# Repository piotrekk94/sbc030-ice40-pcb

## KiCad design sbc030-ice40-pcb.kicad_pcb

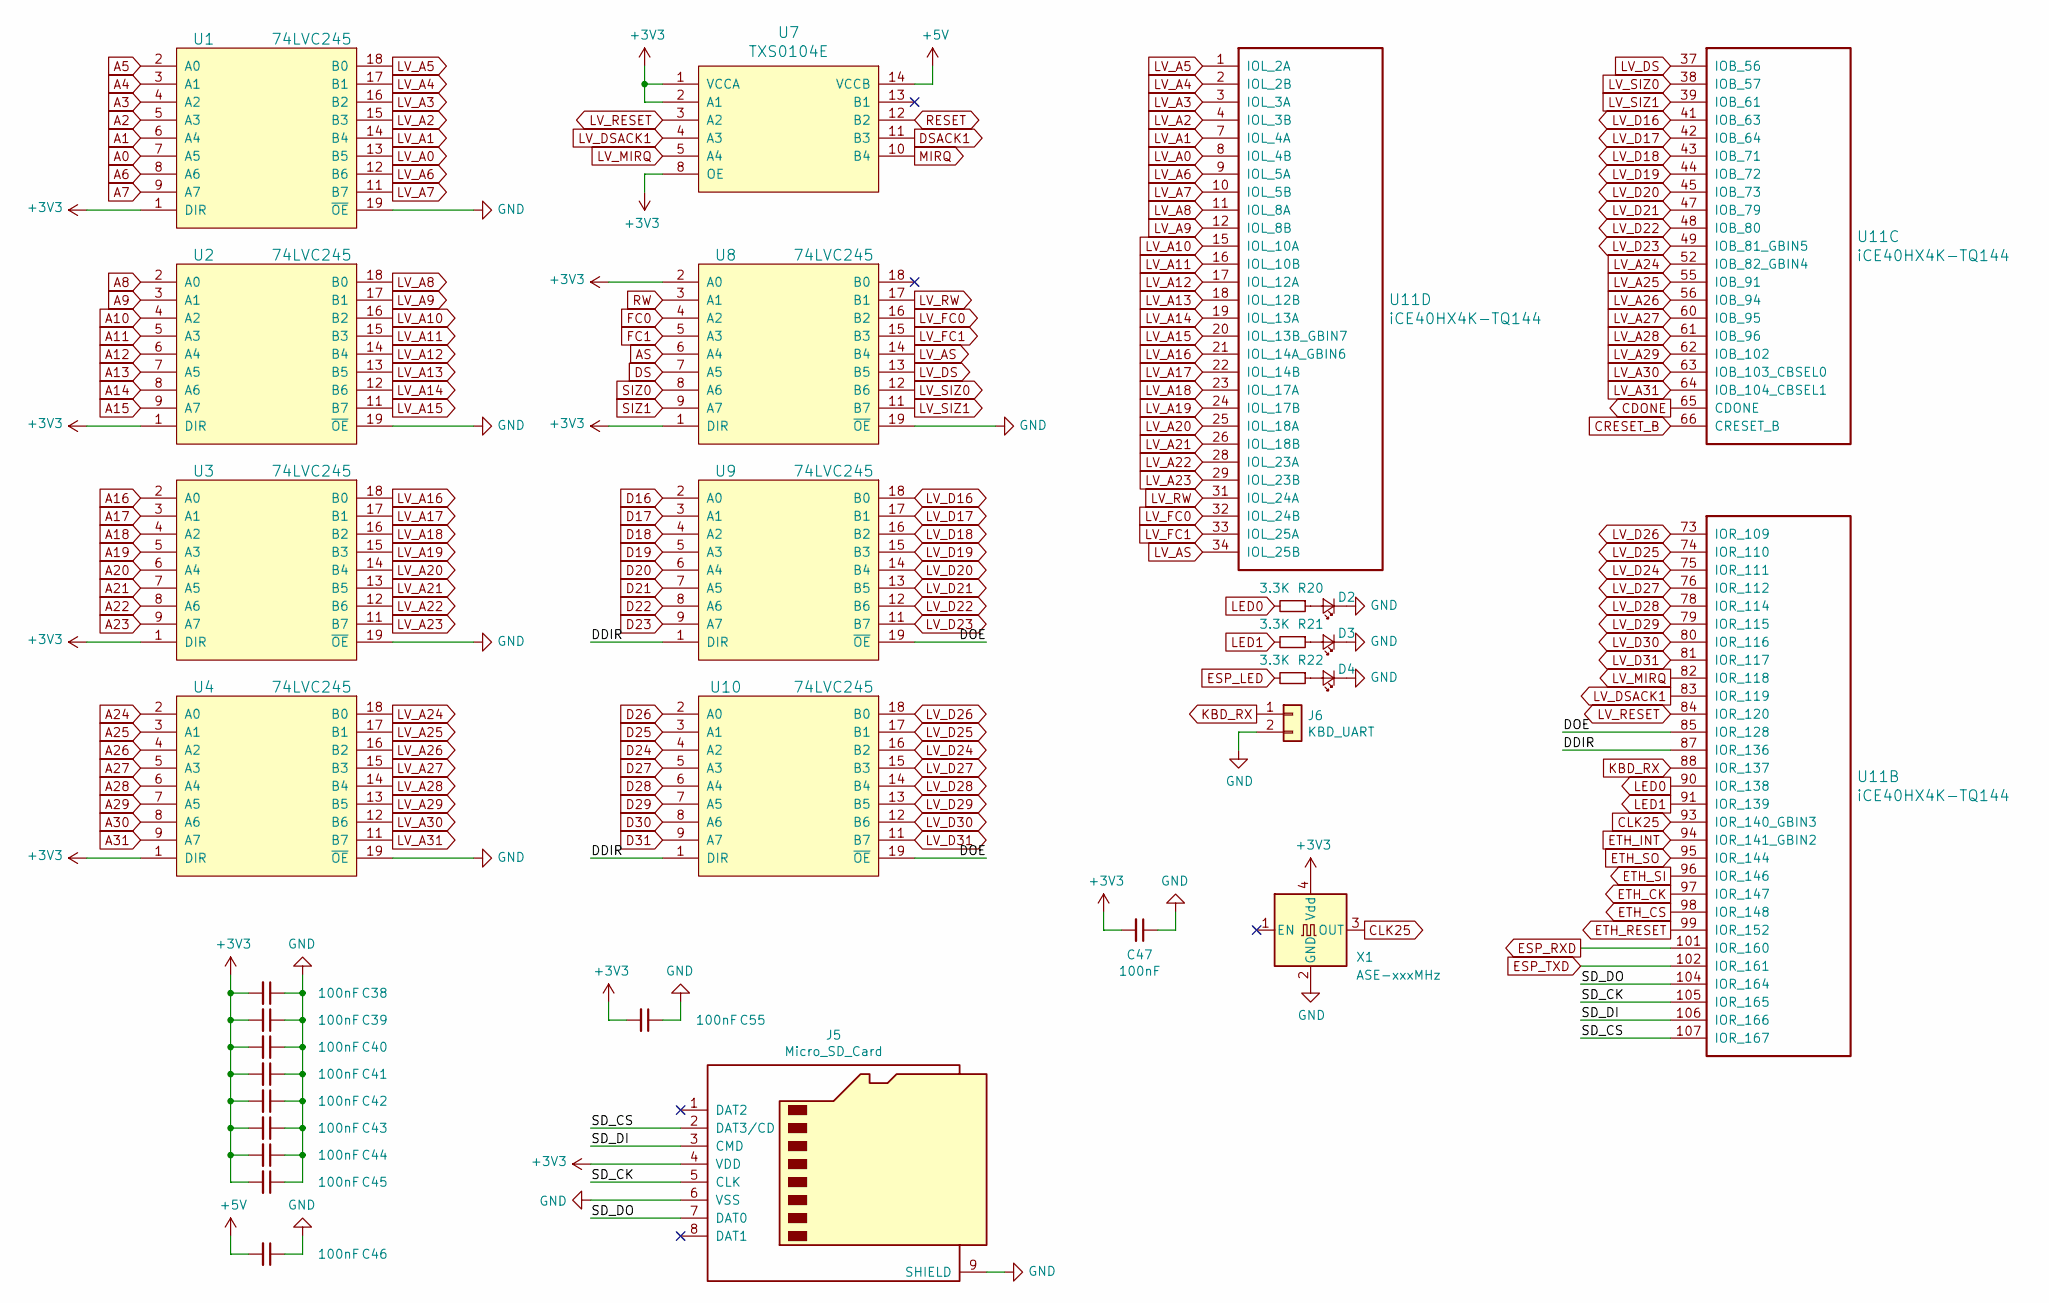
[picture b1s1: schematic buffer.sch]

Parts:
C38, C39, C40, C41, C42, C43, C44, C45, C46, C47, C55: 100nF; C_0603_1608Metric
D2, D3, D4: LED_Small; LED_0603_1608Metric
J5: Micro_SD_Card; microSD_HC_Wuerth_693072010801
J6: KBD_UART; PinHeader_1x02_P2.54mm_Vertical
R20, R21, R22: 3.3K; R_0603_1608Metric
U1, U2, U3, U4, U8, U9, U10: 74LVC245; TSSOP-20_4.4x6.5mm_P0.65mm
U7: TXS0104E; TSSOP-14_4.4x5mm_P0.65mm
U11: iCE40HX4K-TQ144; LQFP-144_20x20mm_P0.5mm
X1: ASE-xxxMHz; Oscillator_SMD_Abracon_ASE-4Pin_3.2x2.5mm

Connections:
+3V3: C38.2, C39.2, C40.2, C41.2, C42.2, C43.2, C44.2, C45.2, C47.2, C55.2, J5.4 (VDD), U1.1 (DIR), U1.20 (VCC), U2.1 (DIR), U2.20 (VCC), U3.1 (DIR), U3.20 (VCC), U4.1 (DIR), U4.20 (VCC), U7.1 (VCCA), U7.2 (A1), U7.8 (OE), U8.1 (DIR), U8.2 (A0), U8.20 (VCC), U9.20 (VCC), U10.20 (VCC), X1.4 (Vdd); also elsewhere on the board
+5V: C46.2, U7.14 (VCCB); also elsewhere on the board
/IO Buffers/DDIR: U9.1 (DIR), U10.1 (DIR), U11.87 (IOR_136)
/IO Buffers/DOE: U9.19 (~OE), U10.19 (~OE), U11.85 (IOR_128)
/IO Buffers/SD_CK: J5.5 (CLK), U11.105 (IOR_165)
/IO Buffers/SD_CS: J5.2 (DAT3/CD), U11.107 (IOR_167)
/IO Buffers/SD_DI: J5.3 (CMD), U11.106 (IOR_166)
/IO Buffers/SD_DO: J5.7 (DAT0), U11.104 (IOR_164)
A0: U1.7 (A5); also elsewhere on the board
A1: U1.6 (A4); also elsewhere on the board
A2: U1.5 (A3); also elsewhere on the board
A3: U1.4 (A2); also elsewhere on the board
A4: U1.3 (A1); also elsewhere on the board
A5: U1.2 (A0); also elsewhere on the board
A6: U1.8 (A6); also elsewhere on the board
A7: U1.9 (A7); also elsewhere on the board
A8: U2.2 (A0); also elsewhere on the board
A9: U2.3 (A1); also elsewhere on the board
A10: U2.4 (A2); also elsewhere on the board
A11: U2.5 (A3); also elsewhere on the board
A12: U2.6 (A4); also elsewhere on the board
A13: U2.7 (A5); also elsewhere on the board
A14: U2.8 (A6); also elsewhere on the board
A15: U2.9 (A7); also elsewhere on the board
A16: U3.2 (A0); also elsewhere on the board
A17: U3.3 (A1); also elsewhere on the board
A18: U3.4 (A2); also elsewhere on the board
A19: U3.5 (A3); also elsewhere on the board
A20: U3.6 (A4); also elsewhere on the board
A21: U3.7 (A5); also elsewhere on the board
A22: U3.8 (A6); also elsewhere on the board
A23: U3.9 (A7); also elsewhere on the board
A24: U4.2 (A0); also elsewhere on the board
A25: U4.3 (A1); also elsewhere on the board
A26: U4.4 (A2); also elsewhere on the board
A27: U4.5 (A3); also elsewhere on the board
A28: U4.6 (A4); also elsewhere on the board
A29: U4.7 (A5); also elsewhere on the board
A30: U4.8 (A6); also elsewhere on the board
A31: U4.9 (A7); also elsewhere on the board
AS: U8.6 (A4); also elsewhere on the board
CDONE: U11.65 (CDONE); also elsewhere on the board
CLK25: U11.93 (IOR_140_GBIN3), X1.3 (OUT); also elsewhere on the board
CRESET_B: U11.66 (CRESET_B); also elsewhere on the board
D16: U9.2 (A0); also elsewhere on the board
D17: U9.3 (A1); also elsewhere on the board
D18: U9.4 (A2); also elsewhere on the board
D19: U9.5 (A3); also elsewhere on the board
D20: U9.6 (A4); also elsewhere on the board
D21: U9.7 (A5); also elsewhere on the board
D22: U9.8 (A6); also elsewhere on the board
D23: U9.9 (A7); also elsewhere on the board
D24: U10.4 (A2); also elsewhere on the board
D25: U10.3 (A1); also elsewhere on the board
D26: U10.2 (A0); also elsewhere on the board
D27: U10.5 (A3); also elsewhere on the board
D28: U10.6 (A4); also elsewhere on the board
D29: U10.7 (A5); also elsewhere on the board
D30: U10.8 (A6); also elsewhere on the board
D31: U10.9 (A7); also elsewhere on the board
DS: U8.7 (A5); also elsewhere on the board
DSACK1: U7.11 (B3); also elsewhere on the board
ESP_LED: R22.2; also elsewhere on the board
ESP_RXD: U11.101 (IOR_160); also elsewhere on the board
ESP_TXD: U11.102 (IOR_161); also elsewhere on the board
ETH_CK: U11.97 (IOR_147); also elsewhere on the board
ETH_CS: U11.98 (IOR_148); also elsewhere on the board
ETH_INT: U11.94 (IOR_141_GBIN2); also elsewhere on the board
ETH_RESET: U11.99 (IOR_152); also elsewhere on the board
ETH_SI: U11.96 (IOR_146); also elsewhere on the board
ETH_SO: U11.95 (IOR_144); also elsewhere on the board
FC0: U8.4 (A2); also elsewhere on the board
FC1: U8.5 (A3); also elsewhere on the board
GND: C38.1, C39.1, C40.1, C41.1, C42.1, C43.1, C44.1, C45.1, C46.1, C47.1, C55.1, D2.1 (K), D3.1 (K), D4.1 (K), J5.6 (VSS), J5.9 (SHIELD), J6.2, U1.10 (GND), U1.19 (~OE), U2.10 (GND), U2.19 (~OE), U3.10 (GND), U3.19 (~OE), U4.10 (GND), U4.19 (~OE), U7.7 (GND), U8.10 (GND), U8.19 (~OE), U9.10 (GND), U10.10 (GND), X1.2 (GND); also elsewhere on the board
KBD_RX: J6.1, U11.88 (IOR_137)
LED0: R20.2, U11.90 (IOR_138)
LED1: R21.2, U11.91 (IOR_139)
LV_A0: U1.13 (B5), U11.8 (IOL_4B)
LV_A1: U1.14 (B4), U11.7 (IOL_4A)
LV_A2: U1.15 (B3), U11.4 (IOL_3B)
LV_A3: U1.16 (B2), U11.3 (IOL_3A)
LV_A4: U1.17 (B1), U11.2 (IOL_2B)
LV_A5: U1.18 (B0), U11.1 (IOL_2A)
LV_A6: U1.12 (B6), U11.9 (IOL_5A)
LV_A7: U1.11 (B7), U11.10 (IOL_5B)
LV_A8: U2.18 (B0), U11.11 (IOL_8A)
LV_A9: U2.17 (B1), U11.12 (IOL_8B)
LV_A10: U2.16 (B2), U11.15 (IOL_10A)
LV_A11: U2.15 (B3), U11.16 (IOL_10B)
LV_A12: U2.14 (B4), U11.17 (IOL_12A)
LV_A13: U2.13 (B5), U11.18 (IOL_12B)
LV_A14: U2.12 (B6), U11.19 (IOL_13A)
LV_A15: U2.11 (B7), U11.20 (IOL_13B_GBIN7)
LV_A16: U3.18 (B0), U11.21 (IOL_14A_GBIN6)
LV_A17: U3.17 (B1), U11.22 (IOL_14B)
LV_A18: U3.16 (B2), U11.23 (IOL_17A)
LV_A19: U3.15 (B3), U11.24 (IOL_17B)
LV_A20: U3.14 (B4), U11.25 (IOL_18A)
LV_A21: U3.13 (B5), U11.26 (IOL_18B)
LV_A22: U3.12 (B6), U11.28 (IOL_23A)
LV_A23: U3.11 (B7), U11.29 (IOL_23B)
LV_A24: U4.18 (B0), U11.52 (IOB_82_GBIN4)
LV_A25: U4.17 (B1), U11.55 (IOB_91)
LV_A26: U4.16 (B2), U11.56 (IOB_94)
LV_A27: U4.15 (B3), U11.60 (IOB_95)
LV_A28: U4.14 (B4), U11.61 (IOB_96)
LV_A29: U4.13 (B5), U11.62 (IOB_102)
LV_A30: U4.12 (B6), U11.63 (IOB_103_CBSEL0)
LV_A31: U4.11 (B7), U11.64 (IOB_104_CBSEL1)
LV_AS: U8.14 (B4), U11.34 (IOL_25B)
LV_D16: U9.18 (B0), U11.41 (IOB_63)
LV_D17: U9.17 (B1), U11.42 (IOB_64)
LV_D18: U9.16 (B2), U11.43 (IOB_71)
LV_D19: U9.15 (B3), U11.44 (IOB_72)
LV_D20: U9.14 (B4), U11.45 (IOB_73)
LV_D21: U9.13 (B5), U11.47 (IOB_79)
LV_D22: U9.12 (B6), U11.48 (IOB_80)
LV_D23: U9.11 (B7), U11.49 (IOB_81_GBIN5)
LV_D24: U10.16 (B2), U11.75 (IOR_111)
LV_D25: U10.17 (B1), U11.74 (IOR_110)
LV_D26: U10.18 (B0), U11.73 (IOR_109)
LV_D27: U10.15 (B3), U11.76 (IOR_112)
LV_D28: U10.14 (B4), U11.78 (IOR_114)
LV_D29: U10.13 (B5), U11.79 (IOR_115)
LV_D30: U10.12 (B6), U11.80 (IOR_116)
LV_D31: U10.11 (B7), U11.81 (IOR_117)
LV_DS: U8.13 (B5), U11.37 (IOB_56)
LV_DSACK1: U7.4 (A3), U11.83 (IOR_119)
LV_FC0: U8.16 (B2), U11.32 (IOL_24B)
LV_FC1: U8.15 (B3), U11.33 (IOL_25A)
LV_MIRQ: U7.5 (A4), U11.82 (IOR_118)
LV_RESET: U7.3 (A2), U11.84 (IOR_120)
LV_RW: U8.17 (B1), U11.31 (IOL_24A)
LV_SIZ0: U8.12 (B6), U11.38 (IOB_57)
LV_SIZ1: U8.11 (B7), U11.39 (IOB_61)
MIRQ: U7.10 (B4); also elsewhere on the board
unnamed: D2.2 (A), R20.1
unnamed: D3.2 (A), R21.1
unnamed: D4.2 (A), R22.1
RESET: U7.12 (B2); also elsewhere on the board
RW: U8.3 (A1); also elsewhere on the board
SIZ0: U8.8 (A6); also elsewhere on the board
SIZ1: U8.9 (A7); also elsewhere on the board

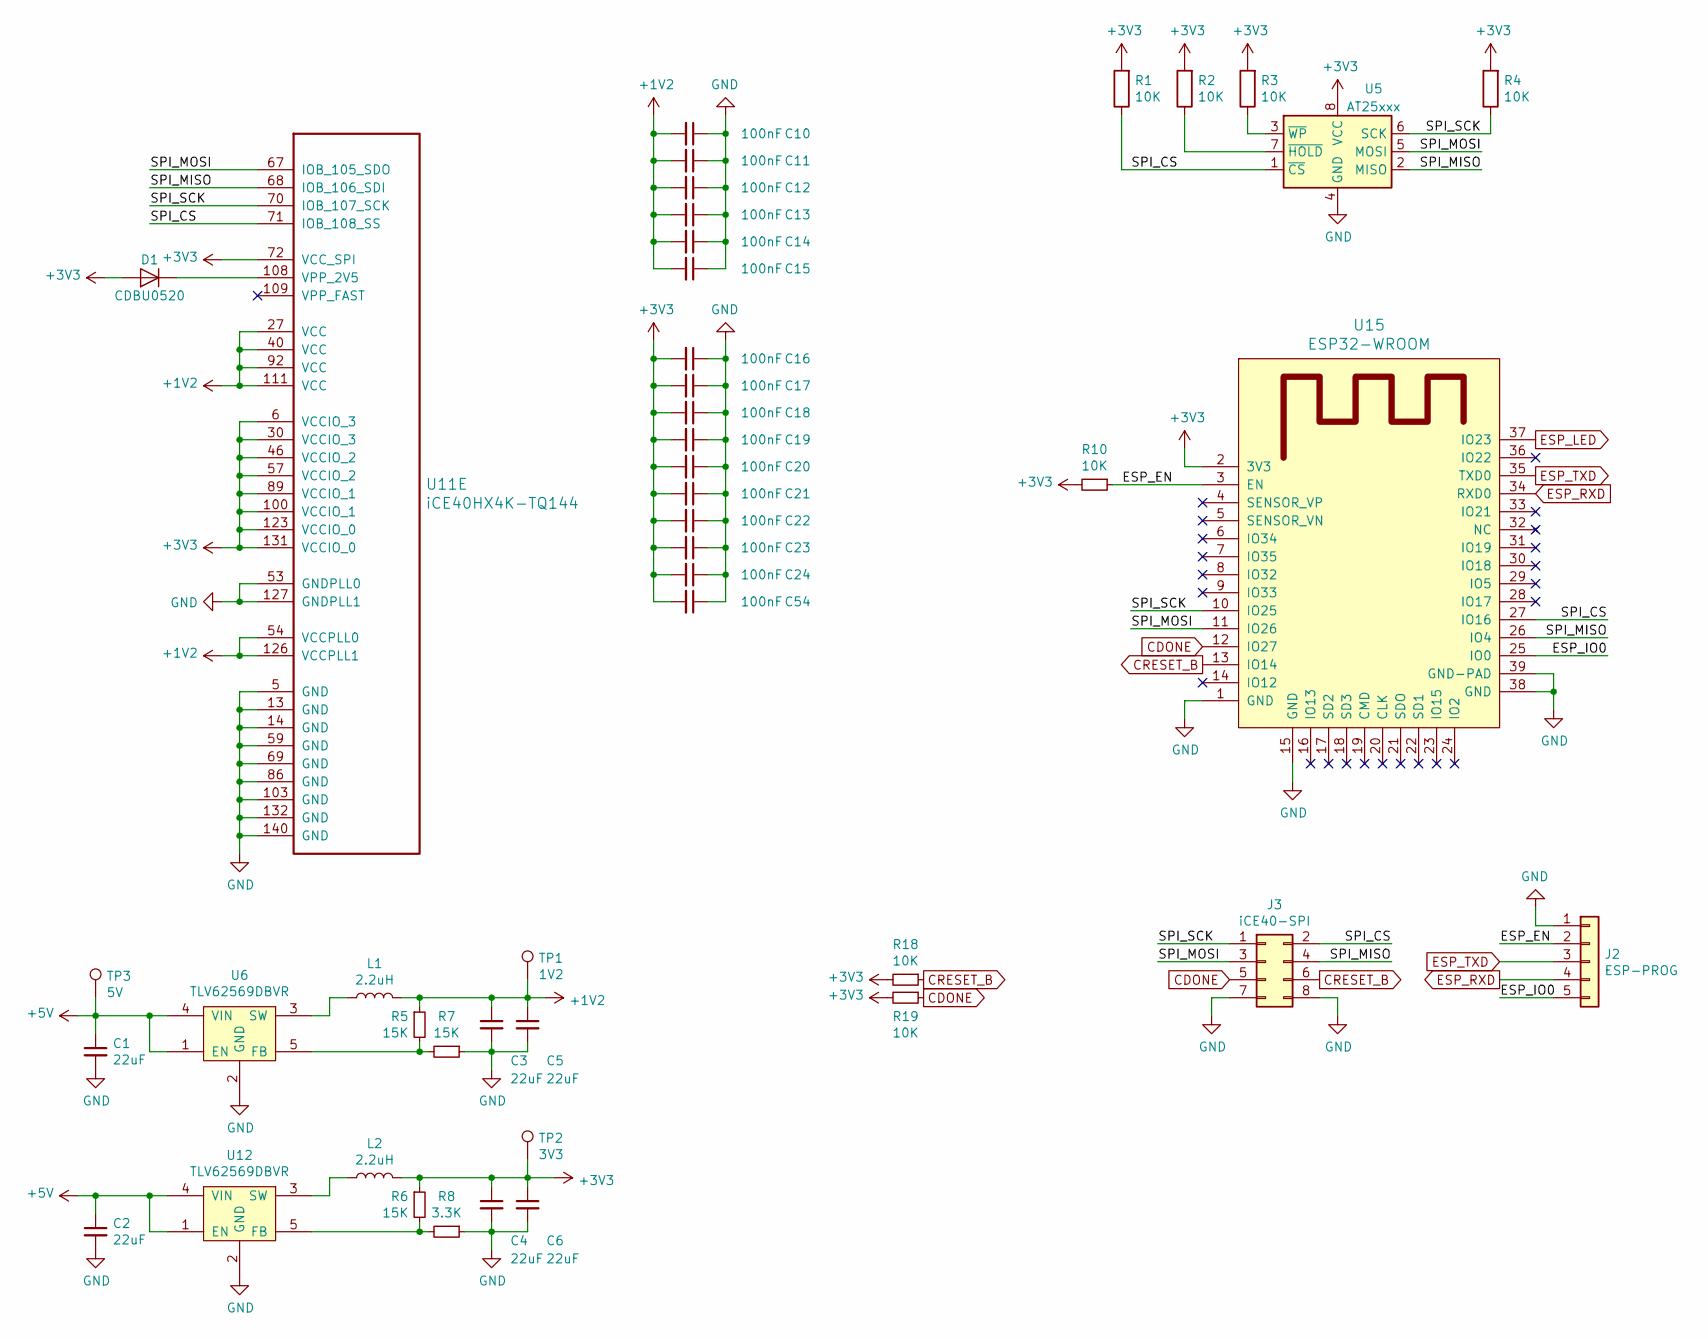
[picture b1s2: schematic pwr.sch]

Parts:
C1, C2, C3, C4, C5, C6: 22uF; C_0805_2012Metric
C10, C11, C12, C13, C14, C15, C16, C17, C18, C19, C20, C21, C22, C23, C24, C54: 100nF; C_0603_1608Metric
D1: CDBU0520; D_0603_1608Metric
J2: ESP-PROG; PinHeader_1x05_P2.54mm_Vertical
J3: iCE40-SPI; PinHeader_2x04_P2.54mm_Vertical
L1, L2: 2.2uH; L_1210_3225Metric
R1, R2, R3, R4, R10, R18, R19: 10K; R_0603_1608Metric
R5, R6, R7: 15K; R_0603_1608Metric
R8: 3.3K; R_0603_1608Metric
TP1: 1V2; TestPoint_Loop_D2.50mm_Drill1.0mm_LowProfile
TP2: 3V3; TestPoint_Loop_D2.50mm_Drill1.0mm_LowProfile
TP3: 5V; TestPoint_Loop_D2.50mm_Drill1.0mm_LowProfile
U5: AT25xxx; SOIC-8_3.9x4.9mm_P1.27mm
U6, U12: TLV62569DBVR; SOT-23-5
U11: iCE40HX4K-TQ144; LQFP-144_20x20mm_P0.5mm
U15: ESP32-WROOM

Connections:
+1V2: C3.1, C5.1, C10.2, C11.2, C12.2, C13.2, C14.2, C15.2, L1.2, R5.1, TP1.1, U11.27 (VCC), U11.40 (VCC), U11.54 (VCCPLL0), U11.92 (VCC), U11.111 (VCC), U11.126 (VCCPLL1)
+3V3: C4.1, C6.1, C16.2, C17.2, C18.2, C19.2, C20.2, C21.2, C22.2, C23.2, C24.2, C54.2, D1.2 (A), L2.2, R1.2, R2.2, R3.2, R4.2, R6.1, R10.2, R18.2, R19.2, TP2.1, U5.8 (VCC), U11.6 (VCCIO_3), U11.30 (VCCIO_3), U11.46 (VCCIO_2), U11.57 (VCCIO_2), U11.72 (VCC_SPI), U11.89 (VCCIO_1), U11.100 (VCCIO_1), U11.123 (VCCIO_0), U11.131 (VCCIO_0), U15.2 (3V3); also elsewhere on the board
+5V: C1.1, C2.1, TP3.1, U6.1 (EN), U6.4 (VIN), U12.1 (EN), U12.4 (VIN); also elsewhere on the board
/Power & Flash/ESP_EN: J2.2, R10.1, U15.3 (EN)
/Power & Flash/ESP_IO0: J2.5, U15.25 (IO0)
/Power & Flash/SPI_CS: J3.2, R1.1, U5.1 (~CS), U11.71 (IOB_108_SS), U15.27 (IO16)
/Power & Flash/SPI_MISO: J3.4, U5.2 (MISO), U11.68 (IOB_106_SDI), U15.26 (IO4)
/Power & Flash/SPI_MOSI: J3.3, U5.5 (MOSI), U11.67 (IOB_105_SDO), U15.11 (IO26)
/Power & Flash/SPI_SCK: J3.1, R4.1, U5.6 (SCK), U11.70 (IOB_107_SCK), U15.10 (IO25)
CDONE: J3.5, R19.1, U15.12 (IO27); also elsewhere on the board
CRESET_B: J3.6, R18.1, U15.13 (IO14); also elsewhere on the board
ESP_LED: U15.37 (IO23); also elsewhere on the board
ESP_RXD: J2.4, U15.34 (RXD0); also elsewhere on the board
ESP_TXD: J2.3, U15.35 (TXD0); also elsewhere on the board
GND: C1.2, C2.2, C3.2, C4.2, C5.2, C6.2, C10.1, C11.1, C12.1, C13.1, C14.1, C15.1, C16.1, C17.1, C18.1, C19.1, C20.1, C21.1, C22.1, C23.1, C24.1, C54.1, J2.1, J3.7, J3.8, R7.1, R8.1, U5.4 (GND), U6.2 (GND), U11.5 (GND), U11.13 (GND), U11.14 (GND), U11.53 (GNDPLL0), U11.59 (GND), U11.69 (GND), U11.86 (GND), U11.103 (GND), U11.127 (GNDPLL1), U11.132 (GND), U11.140 (GND), U12.2 (GND), U15.1 (GND), U15.15 (GND), U15.38 (GND), U15.39 (GND-PAD); also elsewhere on the board
unnamed: D1.1 (K), U11.108 (VPP_2V5)
unnamed: L1.1, U6.3 (SW)
unnamed: L2.1, U12.3 (SW)
unnamed: R2.1, U5.7 (~HOLD)
unnamed: R3.1, U5.3 (~WP)
unnamed: R5.2, R7.2, U6.5 (FB)
unnamed: R6.2, R8.2, U12.5 (FB)

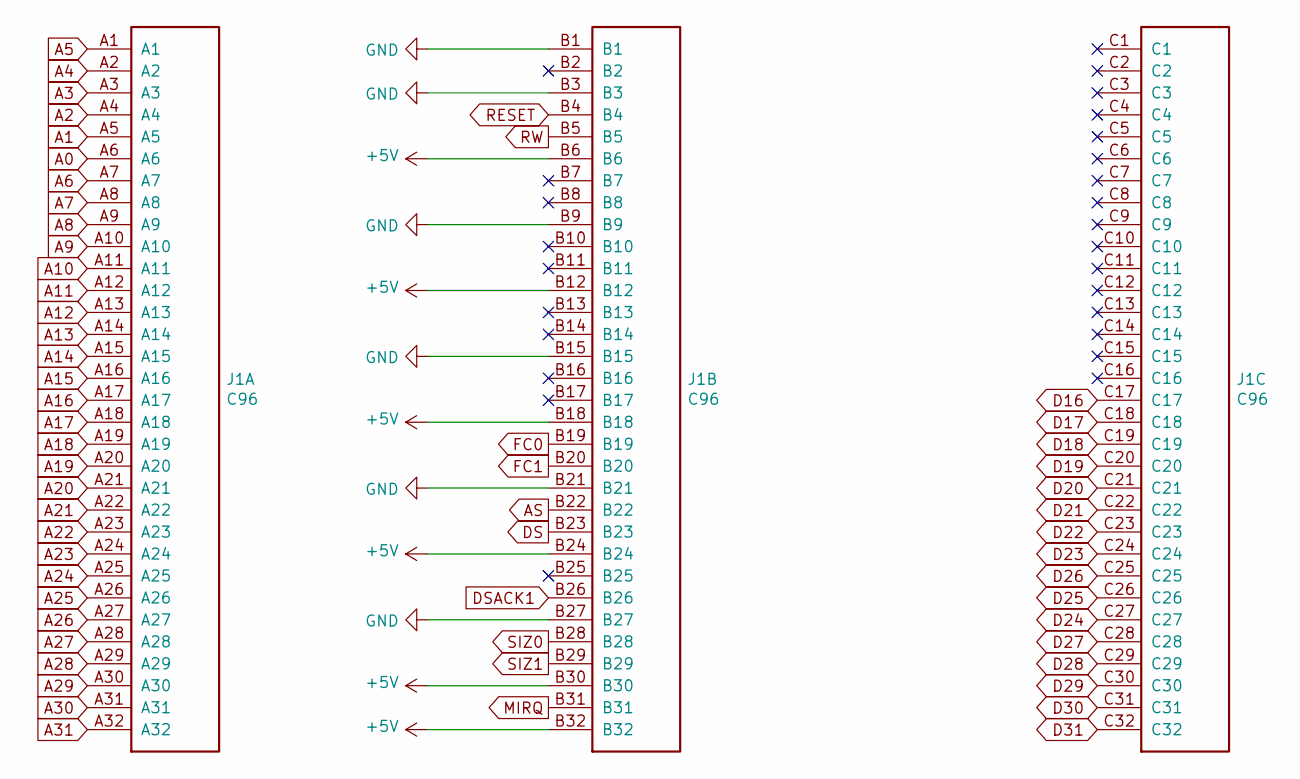
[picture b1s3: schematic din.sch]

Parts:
J1: C96; C96ABCM

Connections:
+5V: J1.B6, J1.B12, J1.B18, J1.B24, J1.B30, J1.B32; also elsewhere on the board
A0: J1.A6; also elsewhere on the board
A1: J1.A5; also elsewhere on the board
A2: J1.A4; also elsewhere on the board
A3: J1.A3; also elsewhere on the board
A4: J1.A2; also elsewhere on the board
A5: J1.A1; also elsewhere on the board
A6: J1.A7; also elsewhere on the board
A7: J1.A8; also elsewhere on the board
A8: J1.A9; also elsewhere on the board
A9: J1.A10; also elsewhere on the board
A10: J1.A11; also elsewhere on the board
A11: J1.A12; also elsewhere on the board
A12: J1.A13; also elsewhere on the board
A13: J1.A14; also elsewhere on the board
A14: J1.A15; also elsewhere on the board
A15: J1.A16; also elsewhere on the board
A16: J1.A17; also elsewhere on the board
A17: J1.A18; also elsewhere on the board
A18: J1.A19; also elsewhere on the board
A19: J1.A20; also elsewhere on the board
A20: J1.A21; also elsewhere on the board
A21: J1.A22; also elsewhere on the board
A22: J1.A23; also elsewhere on the board
A23: J1.A24; also elsewhere on the board
A24: J1.A25; also elsewhere on the board
A25: J1.A26; also elsewhere on the board
A26: J1.A27; also elsewhere on the board
A27: J1.A28; also elsewhere on the board
A28: J1.A29; also elsewhere on the board
A29: J1.A30; also elsewhere on the board
A30: J1.A31; also elsewhere on the board
A31: J1.A32; also elsewhere on the board
AS: J1.B22; also elsewhere on the board
D16: J1.C17; also elsewhere on the board
D17: J1.C18; also elsewhere on the board
D18: J1.C19; also elsewhere on the board
D19: J1.C20; also elsewhere on the board
D20: J1.C21; also elsewhere on the board
D21: J1.C22; also elsewhere on the board
D22: J1.C23; also elsewhere on the board
D23: J1.C24; also elsewhere on the board
D24: J1.C27; also elsewhere on the board
D25: J1.C26; also elsewhere on the board
D26: J1.C25; also elsewhere on the board
D27: J1.C28; also elsewhere on the board
D28: J1.C29; also elsewhere on the board
D29: J1.C30; also elsewhere on the board
D30: J1.C31; also elsewhere on the board
D31: J1.C32; also elsewhere on the board
DS: J1.B23; also elsewhere on the board
DSACK1: J1.B26; also elsewhere on the board
FC0: J1.B19; also elsewhere on the board
FC1: J1.B20; also elsewhere on the board
GND: J1.B1, J1.B3, J1.B9, J1.B15, J1.B21, J1.B27; also elsewhere on the board
MIRQ: J1.B31; also elsewhere on the board
RESET: J1.B4; also elsewhere on the board
RW: J1.B5; also elsewhere on the board
SIZ0: J1.B28; also elsewhere on the board
SIZ1: J1.B29; also elsewhere on the board

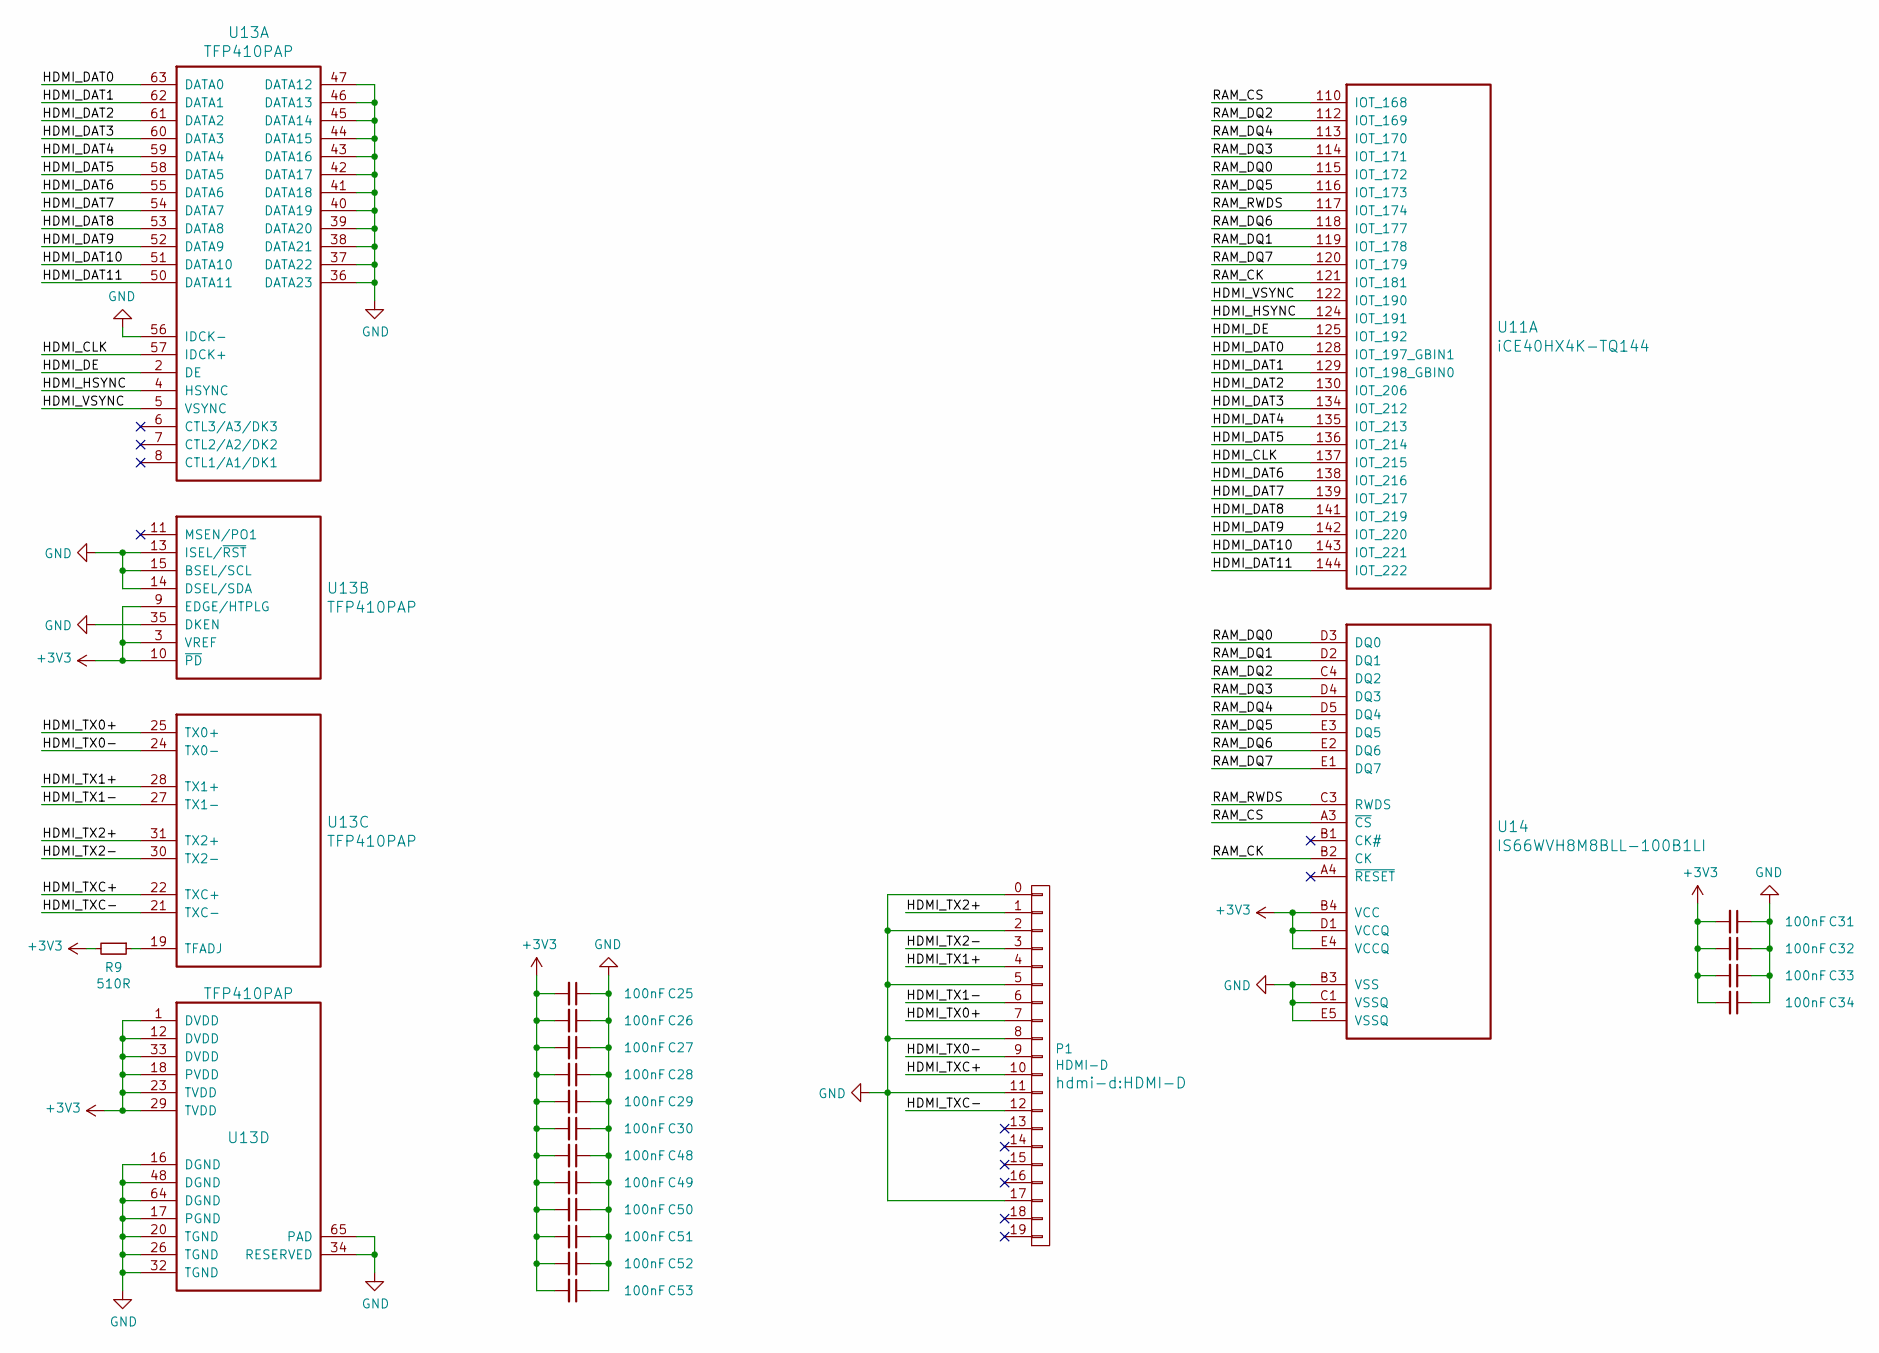
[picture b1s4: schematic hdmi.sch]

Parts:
C25, C26, C27, C28, C29, C30, C31, C32, C33, C34, C48, C49, C50, C51, C52, C53: 100nF; C_0603_1608Metric
P1: HDMI-D
R9: 510R; R_0603_1608Metric
U11: iCE40HX4K-TQ144; LQFP-144_20x20mm_P0.5mm
U13: TFP410PAP; LQFP-64-1EP_10x10mm_P0.5mm_EP6.5x6.5mm
U14: IS66WVH8M8BLL-100B1LI; TFBGA25

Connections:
+3V3: C25.2, C26.2, C27.2, C28.2, C29.2, C30.2, C31.2, C32.2, C33.2, C34.2, C48.2, C49.2, C50.2, C51.2, C52.2, C53.2, R9.2, U13.1 (DVDD), U13.3 (VREF), U13.9 (EDGE/HTPLG), U13.10 (~PD), U13.12 (DVDD), U13.18 (PVDD), U13.23 (TVDD), U13.29 (TVDD), U13.33 (DVDD), U14.B4 (VCC), U14.D1 (VCCQ), U14.E4 (VCCQ); also elsewhere on the board
/HDMI/HDMI_CLK: U11.137 (IOT_215), U13.57 (IDCK+)
/HDMI/HDMI_DAT0: U11.128 (IOT_197_GBIN1), U13.63 (DATA0)
/HDMI/HDMI_DAT1: U11.129 (IOT_198_GBIN0), U13.62 (DATA1)
/HDMI/HDMI_DAT2: U11.130 (IOT_206), U13.61 (DATA2)
/HDMI/HDMI_DAT3: U11.134 (IOT_212), U13.60 (DATA3)
/HDMI/HDMI_DAT4: U11.135 (IOT_213), U13.59 (DATA4)
/HDMI/HDMI_DAT5: U11.136 (IOT_214), U13.58 (DATA5)
/HDMI/HDMI_DAT6: U11.138 (IOT_216), U13.55 (DATA6)
/HDMI/HDMI_DAT7: U11.139 (IOT_217), U13.54 (DATA7)
/HDMI/HDMI_DAT8: U11.141 (IOT_219), U13.53 (DATA8)
/HDMI/HDMI_DAT9: U11.142 (IOT_220), U13.52 (DATA9)
/HDMI/HDMI_DAT10: U11.143 (IOT_221), U13.51 (DATA10)
/HDMI/HDMI_DAT11: U11.144 (IOT_222), U13.50 (DATA11)
/HDMI/HDMI_DE: U11.125 (IOT_192), U13.2 (DE)
/HDMI/HDMI_HSYNC: U11.124 (IOT_191), U13.4 (HSYNC)
/HDMI/HDMI_TX0+: P1.7, U13.25 (TX0+)
/HDMI/HDMI_TX0-: P1.9, U13.24 (TX0-)
/HDMI/HDMI_TX1+: P1.4, U13.28 (TX1+)
/HDMI/HDMI_TX1-: P1.6, U13.27 (TX1-)
/HDMI/HDMI_TX2+: P1.1, U13.31 (TX2+)
/HDMI/HDMI_TX2-: P1.3, U13.30 (TX2-)
/HDMI/HDMI_TXC+: P1.10, U13.22 (TXC+)
/HDMI/HDMI_TXC-: P1.12, U13.21 (TXC-)
/HDMI/HDMI_VSYNC: U11.122 (IOT_190), U13.5 (VSYNC)
/HDMI/RAM_CK: U11.121 (IOT_181), U14.B2 (CK)
/HDMI/RAM_CS: U11.110 (IOT_168), U14.A3 (~CS)
/HDMI/RAM_DQ0: U11.115 (IOT_172), U14.D3 (DQ0)
/HDMI/RAM_DQ1: U11.119 (IOT_178), U14.D2 (DQ1)
/HDMI/RAM_DQ2: U11.112 (IOT_169), U14.C4 (DQ2)
/HDMI/RAM_DQ3: U11.114 (IOT_171), U14.D4 (DQ3)
/HDMI/RAM_DQ4: U11.113 (IOT_170), U14.D5 (DQ4)
/HDMI/RAM_DQ5: U11.116 (IOT_173), U14.E3 (DQ5)
/HDMI/RAM_DQ6: U11.118 (IOT_177), U14.E2 (DQ6)
/HDMI/RAM_DQ7: U11.120 (IOT_179), U14.E1 (DQ7)
/HDMI/RAM_RWDS: U11.117 (IOT_174), U14.C3 (RWDS)
GND: C25.1, C26.1, C27.1, C28.1, C29.1, C30.1, C31.1, C32.1, C33.1, C34.1, C48.1, C49.1, C50.1, C51.1, C52.1, C53.1, P1.0, P1.2, P1.5, P1.8, P1.11, P1.17, U13.13 (ISEL/~RST), U13.14 (DSEL/SDA), U13.15 (BSEL/SCL), U13.16 (DGND), U13.17 (PGND), U13.20 (TGND), U13.26 (TGND), U13.32 (TGND), U13.34 (RESERVED), U13.35 (DKEN), U13.36 (DATA23), U13.37 (DATA22), U13.38 (DATA21), U13.39 (DATA20), U13.40 (DATA19), U13.41 (DATA18), U13.42 (DATA17), U13.43 (DATA16), U13.44 (DATA15), U13.45 (DATA14), U13.46 (DATA13), U13.47 (DATA12), U13.48 (DGND), U13.56 (IDCK-), U13.64 (DGND), U13.65 (PAD), U14.B3 (VSS), U14.C1 (VSSQ), U14.E5 (VSSQ); also elsewhere on the board
unnamed: R9.1, U13.19 (TFADJ)

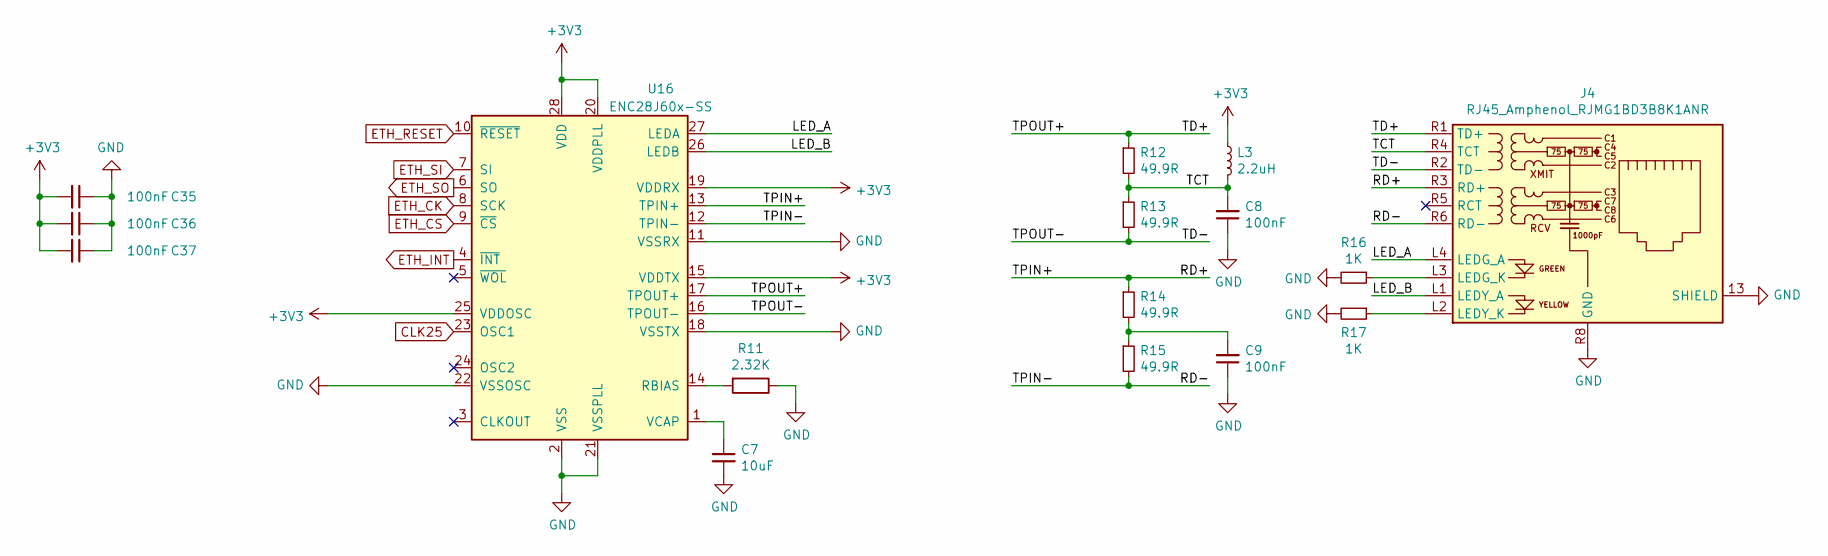
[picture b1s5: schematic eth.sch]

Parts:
C7: 10uF; C_0603_1608Metric
C8, C9, C35, C36, C37: 100nF; C_0603_1608Metric
J4: RJ45_Amphenol_RJMG1BD3B8K1ANR
L3: 2.2uH; L_1210_3225Metric
R11: 2.32K; R_0603_1608Metric
R12, R13, R14, R15: 49.9R; R_0603_1608Metric
R16, R17: 1K; R_0603_1608Metric
U16: ENC28J60x-SS; SSOP-28_5.3x10.2mm_P0.65mm

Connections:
+3V3: C35.2, C36.2, C37.2, L3.1, U16.15 (VDDTX), U16.19 (VDDRX), U16.20 (VDDPLL), U16.25 (VDDOSC), U16.28 (VDD); also elsewhere on the board
/Ethernet/LED_A: J4.L4 (LEDG_A), U16.27 (LEDA)
/Ethernet/LED_B: J4.L1 (LEDY_A), U16.26 (LEDB)
/Ethernet/RD+: J4.R3 (RD+), R14.1, U16.13 (TPIN+)
/Ethernet/RD-: J4.R6 (RD-), R15.2, U16.12 (TPIN-)
/Ethernet/TCT: C8.2, J4.R4 (TCT), L3.2, R12.2, R13.1
/Ethernet/TD+: J4.R1 (TD+), R12.1, U16.17 (TPOUT+)
/Ethernet/TD-: J4.R2 (TD-), R13.2, U16.16 (TPOUT-)
CLK25: U16.23 (OSC1); also elsewhere on the board
ETH_CK: U16.8 (SCK); also elsewhere on the board
ETH_CS: U16.9 (~CS); also elsewhere on the board
ETH_INT: U16.4 (~INT); also elsewhere on the board
ETH_RESET: U16.10 (~RESET); also elsewhere on the board
ETH_SI: U16.7 (SI); also elsewhere on the board
ETH_SO: U16.6 (SO); also elsewhere on the board
GND: C7.2, C8.1, C9.1, C35.1, C36.1, C37.1, J4.13 (SHIELD), J4.R8 (GND), R11.1, R16.2, R17.2, U16.2 (VSS), U16.11 (VSSRX), U16.18 (VSSTX), U16.21 (VSSPLL), U16.22 (VSSOSC); also elsewhere on the board
unnamed: C7.1, U16.1 (VCAP)
unnamed: C9.2, R14.2, R15.1
unnamed: J4.L2 (LEDY_K), R17.1
unnamed: J4.L3 (LEDG_K), R16.1
unnamed: R11.2, U16.14 (RBIAS)

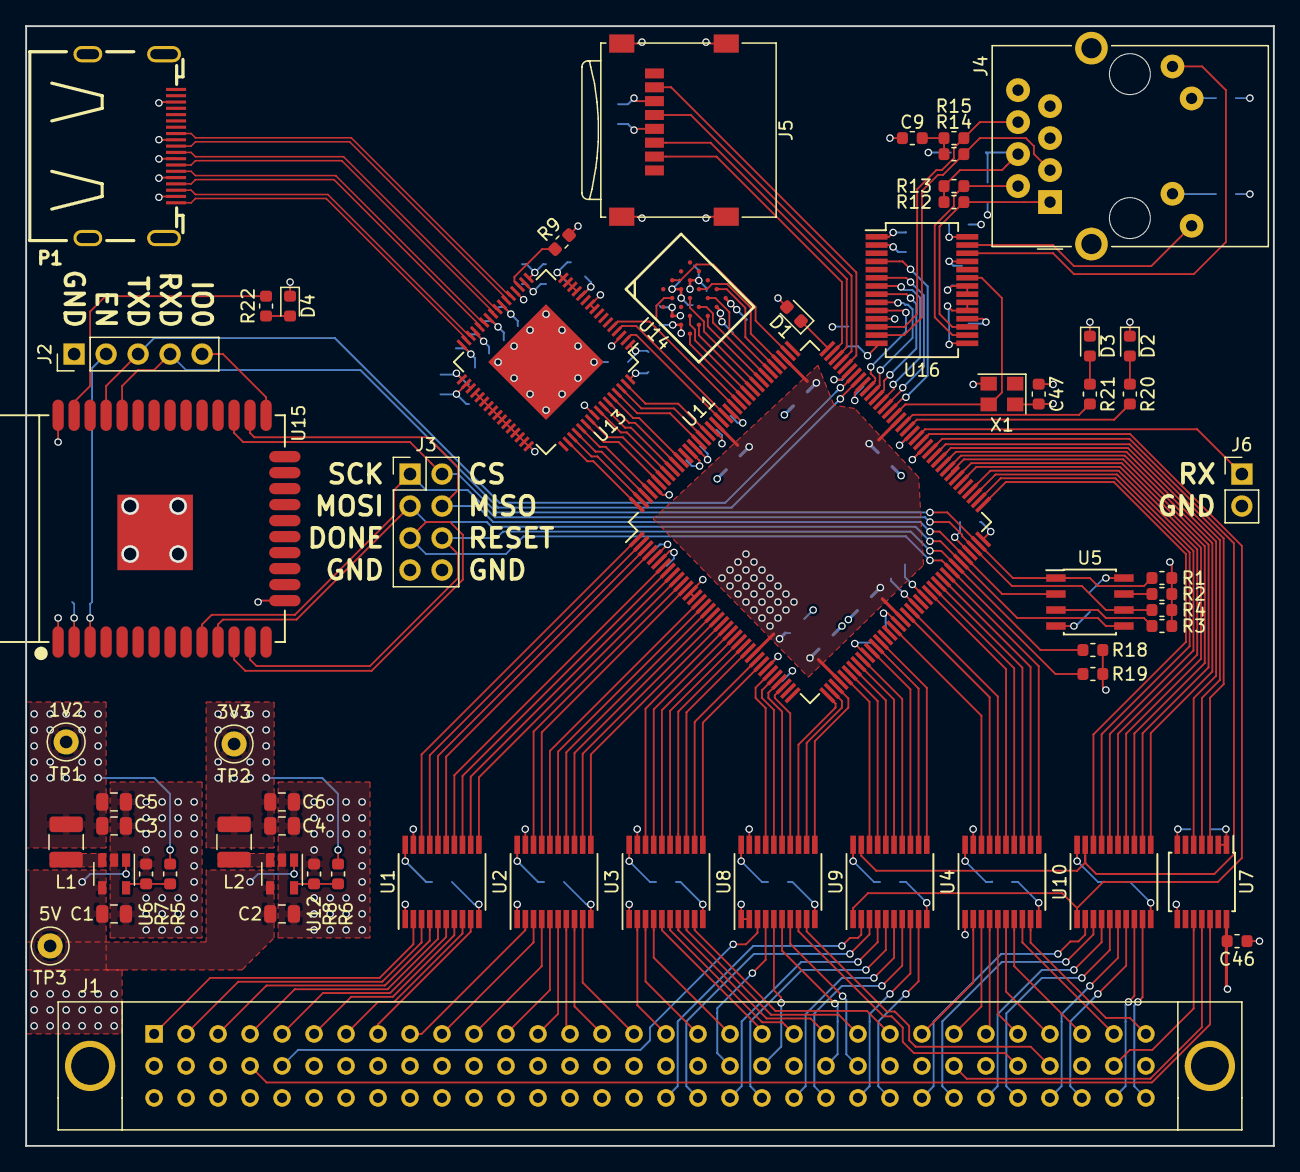
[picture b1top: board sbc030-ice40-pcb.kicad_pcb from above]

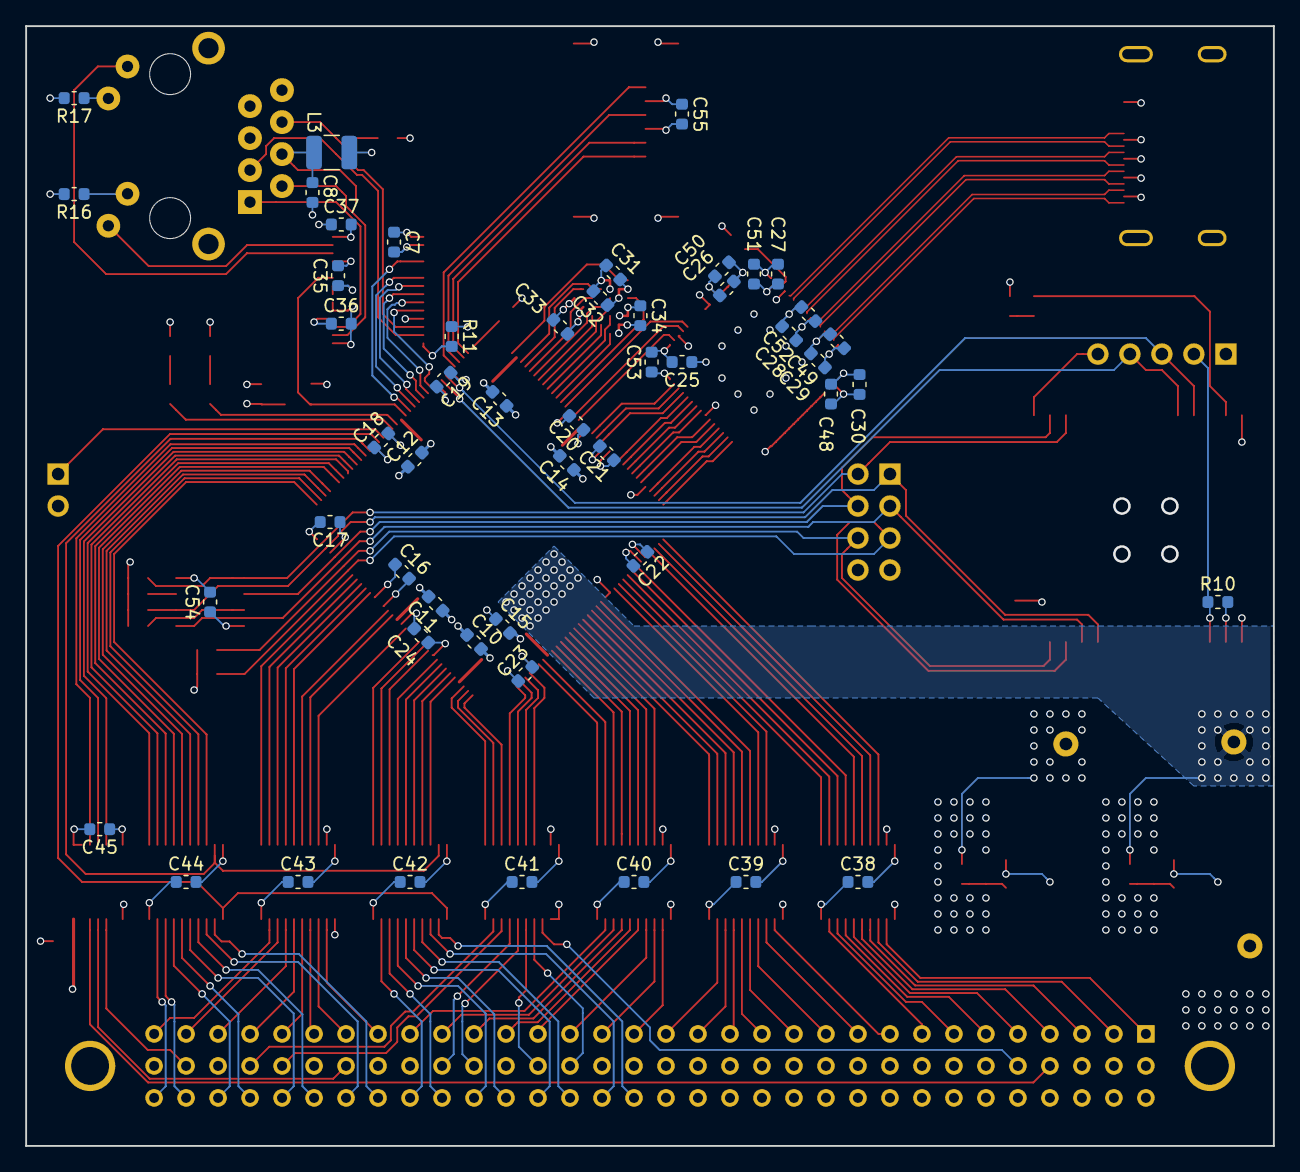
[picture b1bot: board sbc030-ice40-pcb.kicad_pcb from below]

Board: 4 copper layers, 99.1 x 88.9 mm, 111 parts (51 on the bottom side), 205 nets.
